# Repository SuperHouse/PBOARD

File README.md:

Power Breakout Board
==========================
Copyright 2018 SuperHouse Automation Pty Ltd  www.superhouse.tv  

A simple power distribution board using 2.1mm DC sockets. Designed to
fit into a OODTY sized project box.

  http://www.superhouse.tv/pboard

INSTALLATION
------------
The design is saved as an EAGLE project. EAGLE PCB design software is
available from www.cadsoftusa.com free for non-commercial use. To use
this project download it and place the directory containing these files
into the "eagle" directory on your computer. Then open EAGLE and
navigate to the project.

DISTRIBUTION
------------
The specific terms of distribution of this project are governed by the
license referenced below.

LICENSE
-------
Licensed under the TAPR Open Hardware License (www.tapr.org/OHL).
The "license" folder within this repository also contains a copy of
this license in plain text format.

CREDITS
-------
Designed by Jonathan Oxer (jon@oxer.com.au)

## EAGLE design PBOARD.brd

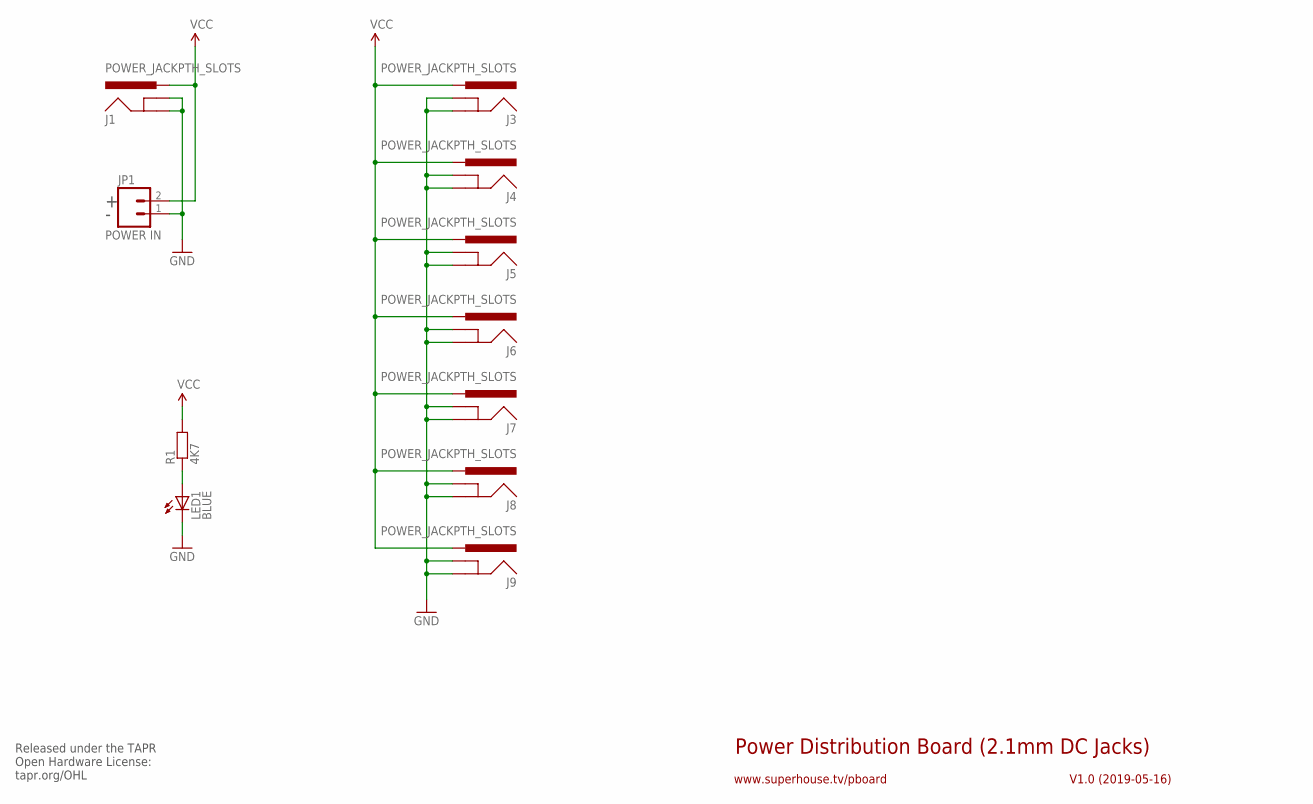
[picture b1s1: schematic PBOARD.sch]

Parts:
J1, J3, J4, J5, J6, J7, J8, J9: POWER_JACKPTH_SLOTS; POWER_JACK_PTH_SLOTS
JP1: POWER IN; SCREWTERMINAL-5MM-2
LED1: BLUE; LED3MM
R1: 4K7; AXIAL-0.3

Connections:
GND: J1.GND, J1.GNDBREAK, J3.GND, J3.GNDBREAK, J4.GND, J4.GNDBREAK, J5.GND, J5.GNDBREAK, J6.GND, J6.GNDBREAK, J7.GND, J7.GNDBREAK, J8.GND, J8.GNDBREAK, J9.GND, J9.GNDBREAK, JP1.1, LED1.K (C)
unnamed: LED1.A, R1.P$1 (1)
VCC: J1.PWR, J3.PWR, J4.PWR, J5.PWR, J6.PWR, J7.PWR, J8.PWR, J9.PWR, JP1.2, R1.P$2 (2)

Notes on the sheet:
Power Distribution Board (2.1mm DC Jacks)
V1.0 (2019-05-16)
www.superhouse.tv/pboard
Released under the TAPR Open Hardware License: tapr.org/OHL

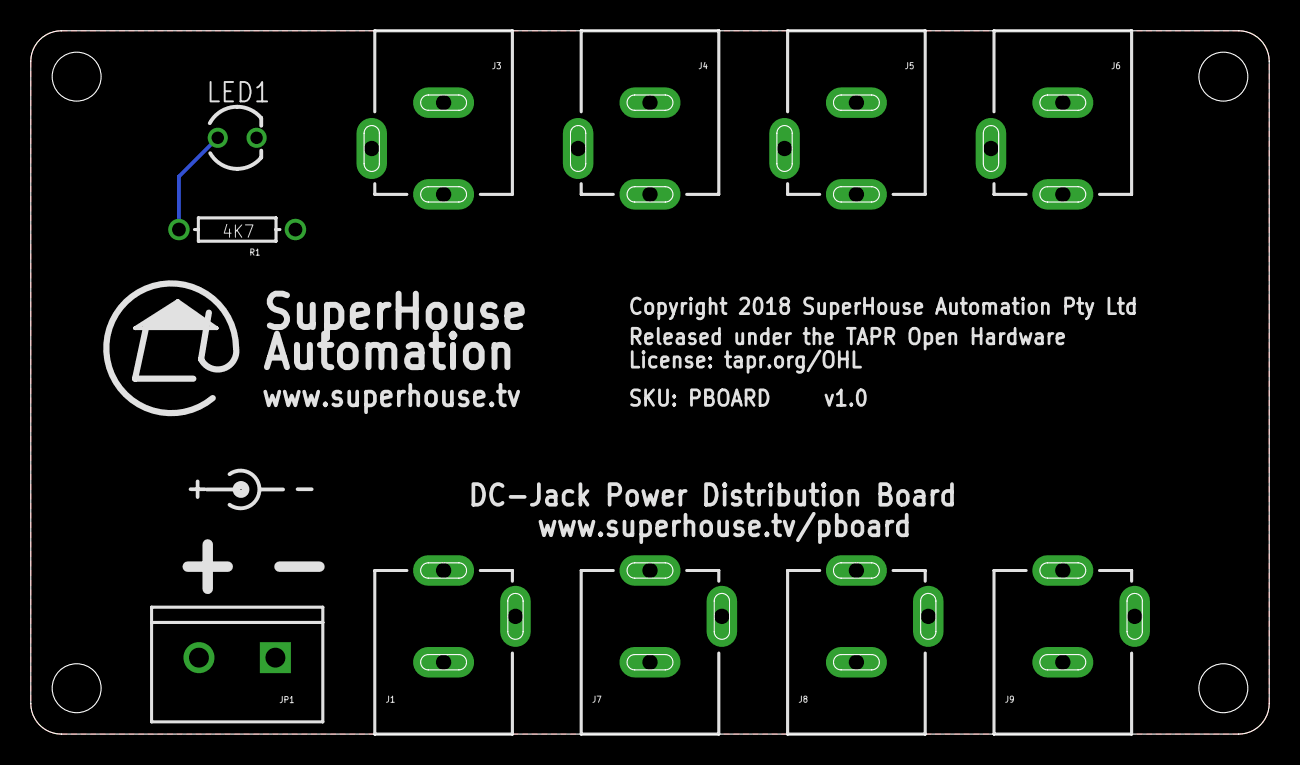
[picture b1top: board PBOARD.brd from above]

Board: 2 copper layers, 81.0 x 46.0 mm, 11 parts (0 on the bottom side), 3 nets.

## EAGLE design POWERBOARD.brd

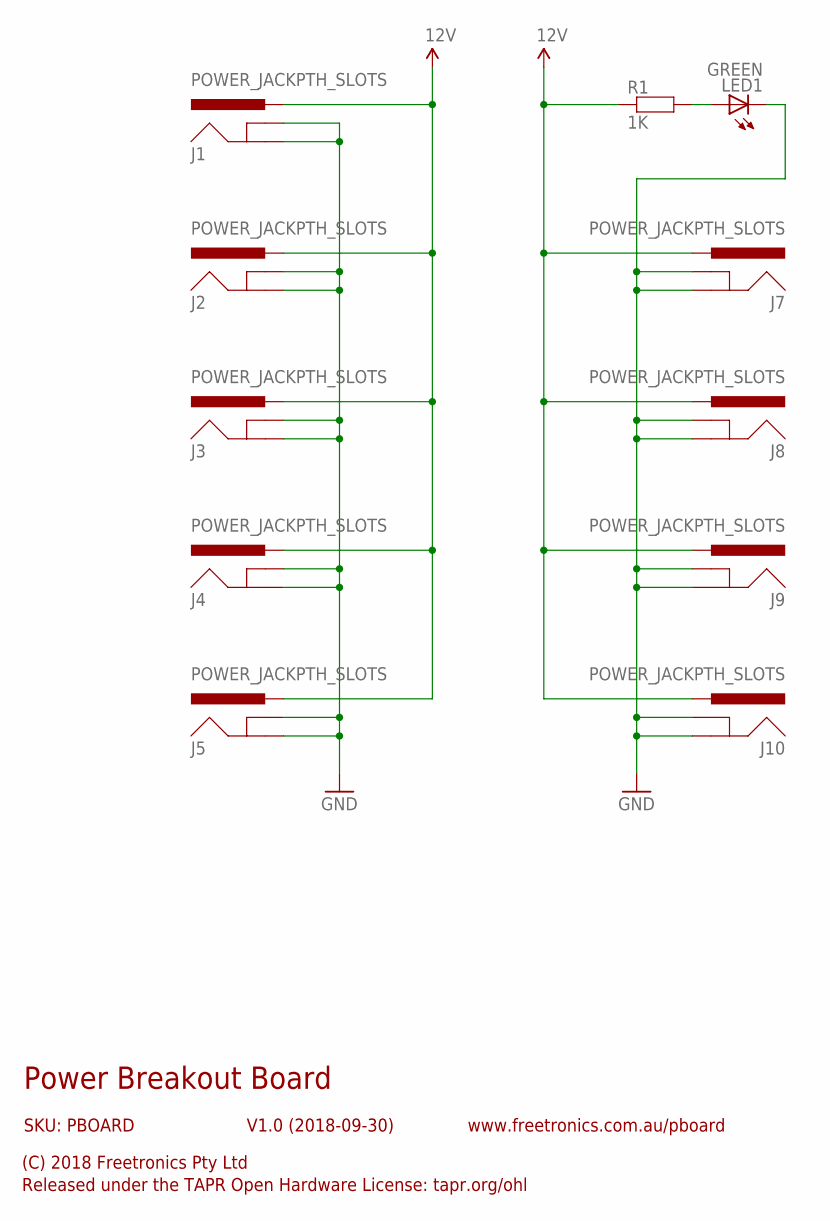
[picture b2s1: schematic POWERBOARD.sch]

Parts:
J1, J2, J3, J4, J5, J7, J8, J9, J10: POWER_JACKPTH_SLOTS; POWER_JACK_PTH_SLOTS
LED1: GREEN; LED3MM
R1: 1K; AXIAL-0.3

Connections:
3.3V: J1.PWR, J2.PWR, J3.PWR, J4.PWR, J5.PWR, J7.PWR, J8.PWR, J9.PWR, J10.PWR, R1.P$1 (1)
GND: J1.GND, J1.GNDBREAK, J2.GND, J2.GNDBREAK, J3.GND, J3.GNDBREAK, J4.GND, J4.GNDBREAK, J5.GND, J5.GNDBREAK, J7.GND, J7.GNDBREAK, J8.GND, J8.GNDBREAK, J9.GND, J9.GNDBREAK, J10.GND, J10.GNDBREAK, LED1.K (C)
unnamed: LED1.A, R1.P$2 (2)

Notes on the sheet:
Power Breakout Board
V1.0 (2018-09-30)
(C) 2018 Freetronics Pty Ltd
Released under the TAPR Open Hardware License: tapr.org/ohl
www.freetronics.com.au/pboard
SKU: PBOARD

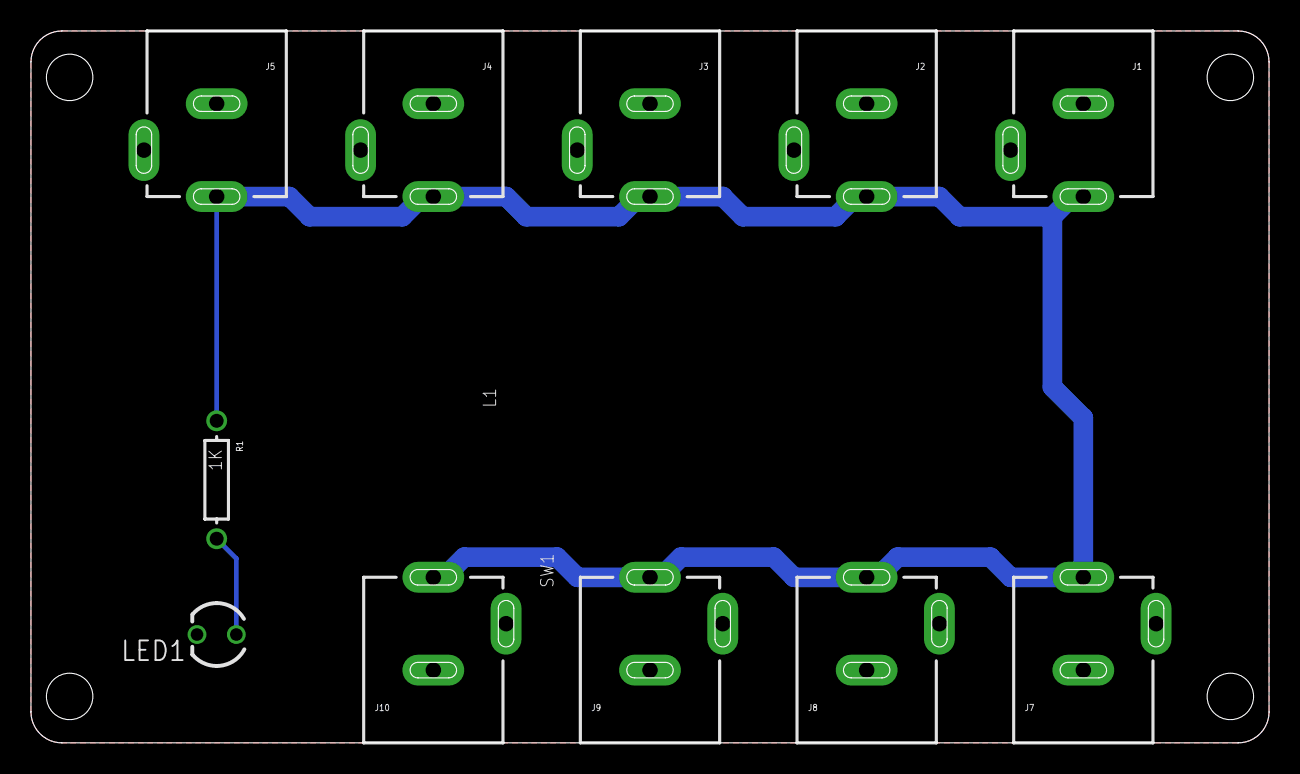
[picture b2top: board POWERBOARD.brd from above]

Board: 2 copper layers, 80.0 x 46.0 mm, 11 parts (0 on the bottom side), 3 nets.

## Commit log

2018-09-30 Initial project import
2019-04-24 Renamed project files
2019-04-24 Merged files from PowerDistributionBoard project
2019-05-21 Added power LED for v1.0 release

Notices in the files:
parts and their libraries:
freetronics-original: Licensing: CC v3.0 Share-Alike You are welcome to use this library for commercial purposes.
